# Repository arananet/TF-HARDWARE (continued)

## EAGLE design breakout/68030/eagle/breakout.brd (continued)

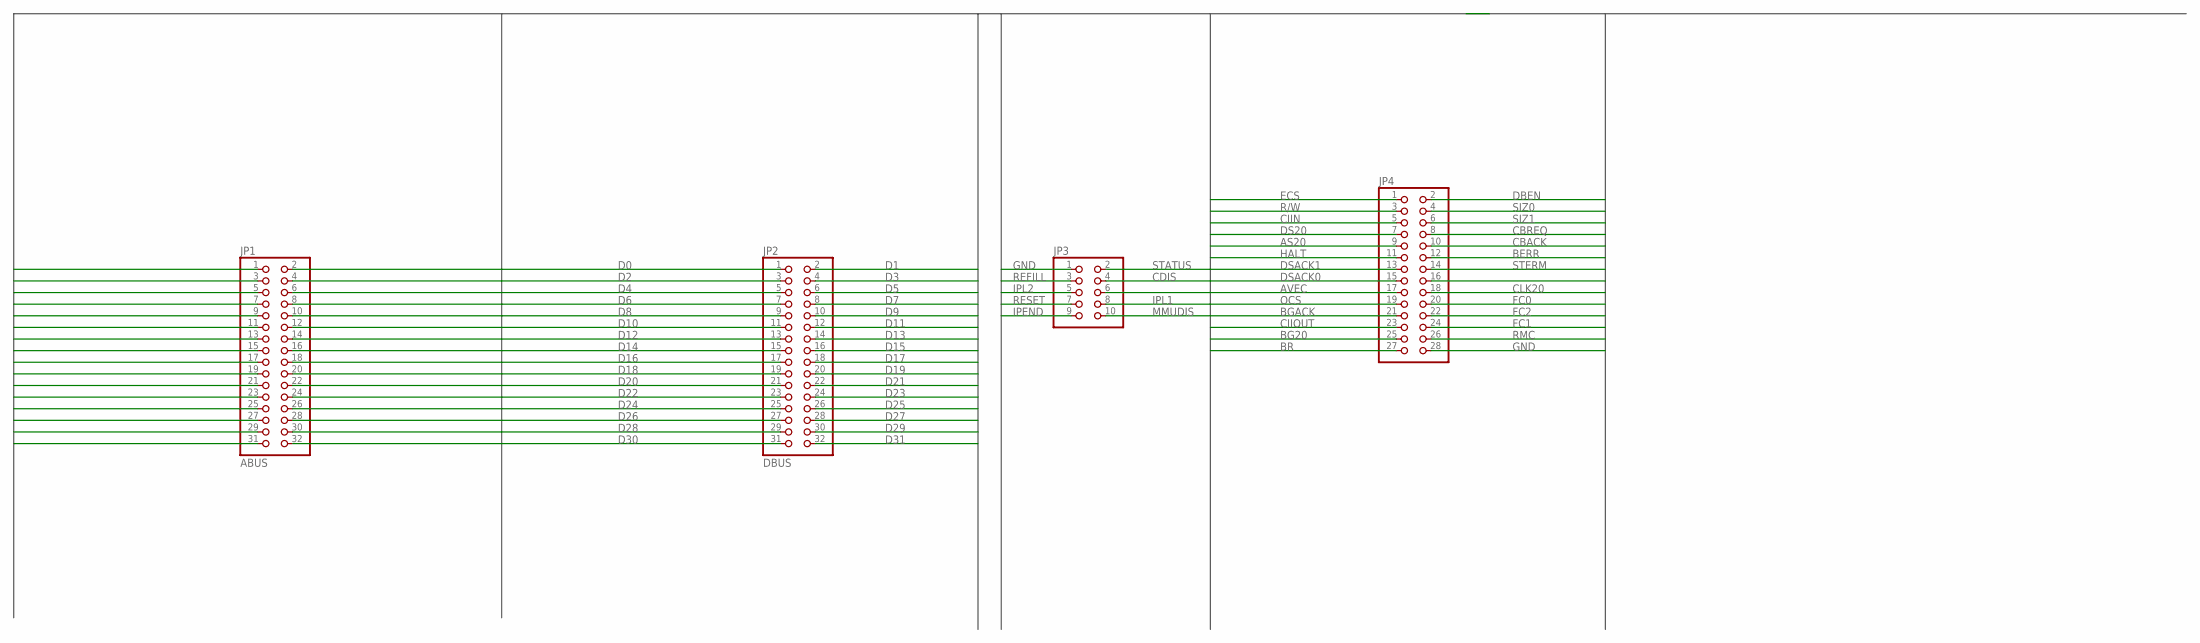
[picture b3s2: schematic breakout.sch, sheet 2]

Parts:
JP1: ABUS; 2X16
JP2: DBUS; 2X16
JP3: PINHD-2X5; 2X05
JP4: PINHD-2X14; 2X14

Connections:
A0: JP1.1; also elsewhere on the board
A1: JP1.2; also elsewhere on the board
A2: JP1.3; also elsewhere on the board
A3: JP1.4; also elsewhere on the board
A4: JP1.5; also elsewhere on the board
A5: JP1.6; also elsewhere on the board
A6: JP1.7; also elsewhere on the board
A7: JP1.8; also elsewhere on the board
A8: JP1.9; also elsewhere on the board
A9: JP1.10; also elsewhere on the board
A10: JP1.11; also elsewhere on the board
A11: JP1.12; also elsewhere on the board
A12: JP1.13; also elsewhere on the board
A13: JP1.14; also elsewhere on the board
A14: JP1.15; also elsewhere on the board
A15: JP1.16; also elsewhere on the board
A16: JP1.17; also elsewhere on the board
A17: JP1.18; also elsewhere on the board
A18: JP1.19; also elsewhere on the board
A19: JP1.20; also elsewhere on the board
A20: JP1.21; also elsewhere on the board
A21: JP1.22; also elsewhere on the board
A22: JP1.23; also elsewhere on the board
A23: JP1.24; also elsewhere on the board
A24: JP1.25; also elsewhere on the board
A25: JP1.26; also elsewhere on the board
A26: JP1.27; also elsewhere on the board
A27: JP1.28; also elsewhere on the board
A28: JP1.29; also elsewhere on the board
A29: JP1.30; also elsewhere on the board
A30: JP1.31; also elsewhere on the board
A31: JP1.32; also elsewhere on the board
AS20: JP4.9; also elsewhere on the board
AVEC: JP4.17; also elsewhere on the board
BERR: JP4.12; also elsewhere on the board
BG20: JP4.25; also elsewhere on the board
BGACK: JP4.21; also elsewhere on the board
BR: JP4.27; also elsewhere on the board
CBACK: JP4.10; also elsewhere on the board
CBREQ: JP4.8; also elsewhere on the board
CDIS: JP3.4; also elsewhere on the board
CIIN: JP4.5; also elsewhere on the board
CIIOUT: JP4.23; also elsewhere on the board
CLK20: JP4.18; also elsewhere on the board
D0: JP2.1; also elsewhere on the board
D1: JP2.2; also elsewhere on the board
D2: JP2.3; also elsewhere on the board
D3: JP2.4; also elsewhere on the board
D4: JP2.5; also elsewhere on the board
D5: JP2.6; also elsewhere on the board
D6: JP2.7; also elsewhere on the board
D7: JP2.8; also elsewhere on the board
D8: JP2.9; also elsewhere on the board
D9: JP2.10; also elsewhere on the board
D10: JP2.11; also elsewhere on the board
D11: JP2.12; also elsewhere on the board
D12: JP2.13; also elsewhere on the board
D13: JP2.14; also elsewhere on the board
D14: JP2.15; also elsewhere on the board
D15: JP2.16; also elsewhere on the board
D16: JP2.17; also elsewhere on the board
D17: JP2.18; also elsewhere on the board
D18: JP2.19; also elsewhere on the board
D19: JP2.20; also elsewhere on the board
D20: JP2.21; also elsewhere on the board
D21: JP2.22; also elsewhere on the board
D22: JP2.23; also elsewhere on the board
D23: JP2.24; also elsewhere on the board
D24: JP2.25; also elsewhere on the board
D25: JP2.26; also elsewhere on the board
D26: JP2.27; also elsewhere on the board
D27: JP2.28; also elsewhere on the board
D28: JP2.29; also elsewhere on the board
D29: JP2.30; also elsewhere on the board
D30: JP2.31; also elsewhere on the board
D31: JP2.32; also elsewhere on the board
DBEN: JP4.2; also elsewhere on the board
DS20: JP4.7; also elsewhere on the board
DSACK0: JP4.15; also elsewhere on the board
DSACK1: JP4.13; also elsewhere on the board
ECS: JP4.1; also elsewhere on the board
FC0: JP4.20; also elsewhere on the board
FC1: JP4.24; also elsewhere on the board
FC2: JP4.22; also elsewhere on the board
GND: JP3.1, JP4.28; also elsewhere on the board
HALT: JP4.11; also elsewhere on the board
IPEND: JP3.9; also elsewhere on the board
IPL0: JP3.6; also elsewhere on the board
IPL1: JP3.8; also elsewhere on the board
IPL2: JP3.5; also elsewhere on the board
MMUDIS: JP3.10; also elsewhere on the board
OCS: JP4.19; also elsewhere on the board
R/W: JP4.3; also elsewhere on the board
REFILL: JP3.3; also elsewhere on the board
RESET: JP3.7; also elsewhere on the board
RMC: JP4.26; also elsewhere on the board
SIZ0: JP4.4; also elsewhere on the board
SIZ1: JP4.6; also elsewhere on the board
STATUS: JP3.2; also elsewhere on the board
STERM: JP4.14; also elsewhere on the board
VCC: JP4.16; also elsewhere on the board

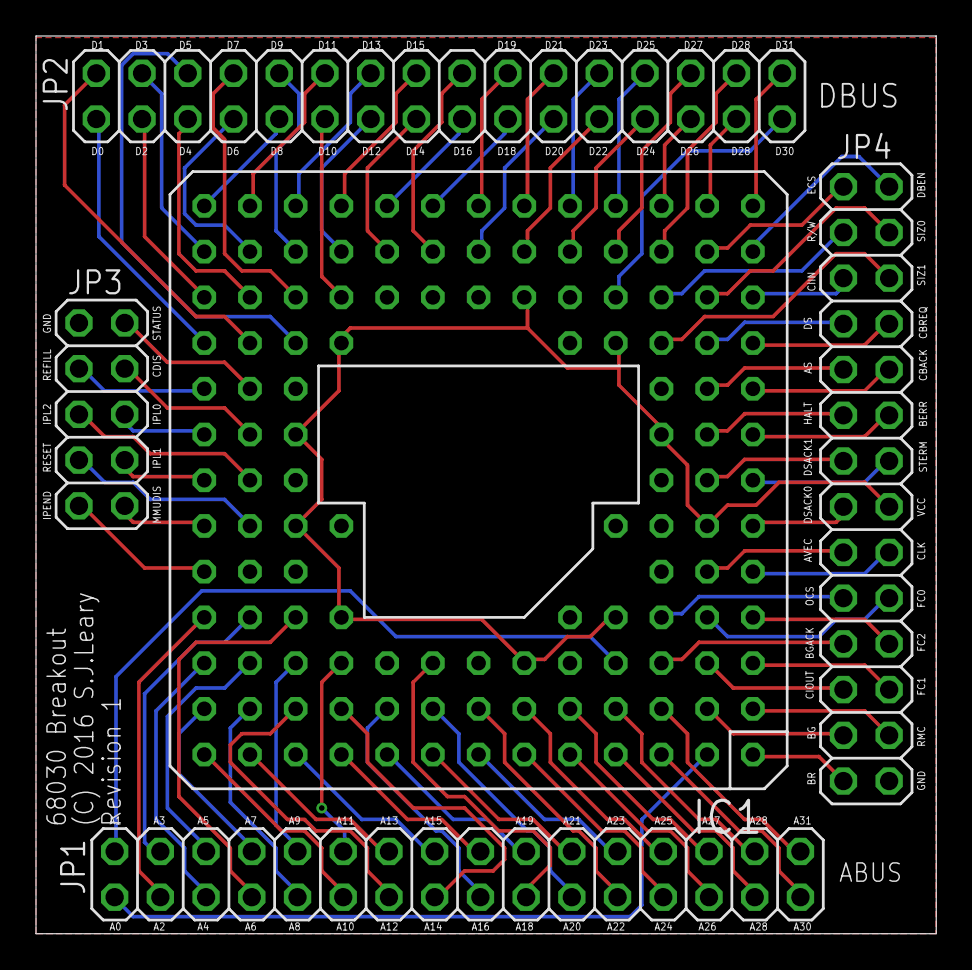
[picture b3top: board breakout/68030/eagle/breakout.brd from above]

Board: 2 copper layers, 50.0 x 49.9 mm, 5 parts (0 on the bottom side), 101 nets.

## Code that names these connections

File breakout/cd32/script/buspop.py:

#!/usr/bin/python
import xml.etree.cElementTree as ET
from xml.dom import minidom
import sys

head = open('tf32brk.sch.head', 'r').read()
target = "CD32_EXPANSION"

tail = """</sheet>
</sheets>
</schematic>
</drawing>
</eagle>"""

tree = ET.parse('tf32brk.sch.head')
doc = tree.getroot()
connect = doc.findall(".//connect")
symbols = doc.findall(".//symbols")
instances = doc.findall(".//instances")
pads = {}

symbol_pins = {}

def eFloat(x):
    return "%.2f" % (x)

def getNetName(name, pinmap):
    try:
        ret = pinmap[name]
    except:
        ret = name
    return ret


for i in range(0,len(connect)):
    pads[connect[i].get("pad")] = connect[i]

for elems in symbols:
    for symbol in elems:
        if symbol.get("name") == target:
            for items in symbol:
                for pin in symbol:
                    if (pin.tag == "pin"):
                        symbol_pins[pin.get("name")] = pin

labelSize = size="1.778"
labelLayer = "95"
layer = "91"
width= "0.1534"
span = 78.74
nets = ET.Element("nets")

pinmap = {"_IPL2":"IPL2", "_IPL1":"IPL1", "_IPL0":"IPL0", "SIZE_1":"SIZ1", "SIZE_0":"SIZ0", "FC_0":"FC0","FC_1":"FC1","FC_2":"FC2", "17MHZ":"CLK17MHZ"}

for pinkey in symbol_pins.keys():
    pin = symbol_pins[pinkey]
    net = ET.SubElement(nets, "net", {"name":getNetName(pinkey,pinmap),"class":"0"})
    for elems in instances:
        for instance in elems:
            if (instance.get("gate") == target):
                part = instance.get("part")
                offsetx = float(instance.get("x"))
                offsety = float(instance.get("y"))
                x = float(pin.get("x")) +offsetx
                y = float(pin.get("y")) +offsety

                segment = ET.SubElement(net, "segment")
                pinref = ET.SubElement(segment, "pinref", part=part, gate="CD32_EXPANSION", pin=pinkey)
                if (x > offsetx):
                    wire = ET.SubElement(segment, "wire", x1=eFloat(x), y1=eFloat(y), x2=eFloat(x + span), y2=eFloat(y), width=width, layer=layer)
                    label = ET.SubElement(segment, "label", x=eFloat(x + span/2), y=eFloat(y), size=labelSize, layer=labelLayer)
                    pass
                else:
                    wire = ET.SubElement(segment, "wire", x1=eFloat(x), y1=eFloat(y), x2=eFloat(x - span), y2=eFloat(y), width=width, layer=layer)
                    label = ET.SubElement(segment, "label", x=eFloat(x - span/2), y=eFloat(y), size=labelSize, layer=labelLayer)
                    pass
print head
ET.dump(nets)
print tail

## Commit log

2017-04-18 Fixed silkscreen
2017-04-26 Bit of a clean up of the silkscreen
2017-04-26 Updating the ucf files for the rev 3
